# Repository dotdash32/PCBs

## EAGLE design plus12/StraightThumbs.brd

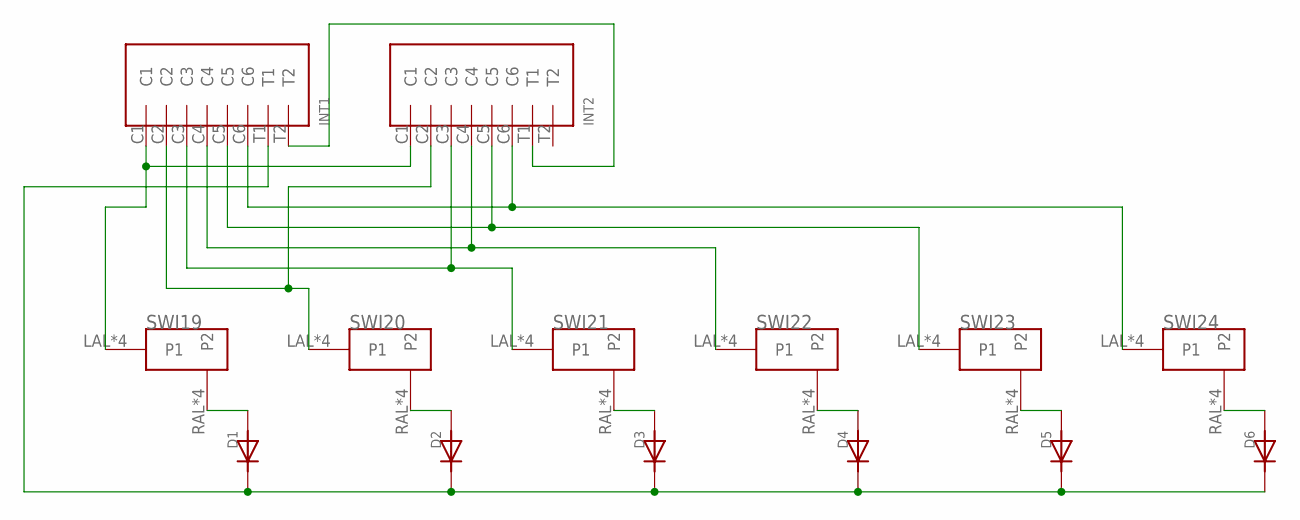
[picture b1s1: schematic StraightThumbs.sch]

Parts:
D1, D2, D3, D4, D5, D6: DIODE; DIODE_COMBO
INT1, INT2: INTRCNNT
SWI19, SWI20, SWI21, SWI22, SWI23, SWI24: MX/ALPSDOUBLESIDED; DOUBLED_MX/ALPS

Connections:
unnamed: D1.ANOSB (AN), D1.ANOST (AN), D1.ANOT (AN), SWI19.RAL (P2), SWI19.RAR (P2), SWI19.RCL (P2), SWI19.RCR (P2)
unnamed: D2.ANOSB (AN), D2.ANOST (AN), D2.ANOT (AN), SWI20.RAL (P2), SWI20.RAR (P2), SWI20.RCL (P2), SWI20.RCR (P2)
unnamed: D3.ANOSB (AN), D3.ANOST (AN), D3.ANOT (AN), SWI21.RAL (P2), SWI21.RAR (P2), SWI21.RCL (P2), SWI21.RCR (P2)
unnamed: D4.ANOSB (AN), D4.ANOST (AN), D4.ANOT (AN), SWI22.RAL (P2), SWI22.RAR (P2), SWI22.RCL (P2), SWI22.RCR (P2)
unnamed: D5.ANOSB (AN), D5.ANOST (AN), D5.ANOT (AN), SWI23.RAL (P2), SWI23.RAR (P2), SWI23.RCL (P2), SWI23.RCR (P2)
unnamed: D6.ANOSB (AN), D6.ANOST (AN), D6.ANOT (AN), SWI24.RAL (P2), SWI24.RAR (P2), SWI24.RCL (P2), SWI24.RCR (P2)
unnamed: INT1.C1, INT2.C1, SWI19.LAL (P1), SWI19.LAR (P1), SWI19.LCL (P1), SWI19.LCR (P1)
unnamed: INT1.C2, INT2.C2, SWI20.LAL (P1), SWI20.LAR (P1), SWI20.LCL (P1), SWI20.LCR (P1)
unnamed: INT1.C3, INT2.C3, SWI21.LAL (P1), SWI21.LAR (P1), SWI21.LCL (P1), SWI21.LCR (P1)
unnamed: INT1.C4, INT2.C4, SWI22.LAL (P1), SWI22.LAR (P1), SWI22.LCL (P1), SWI22.LCR (P1)
unnamed: INT1.C5, INT2.C5, SWI23.LAL (P1), SWI23.LAR (P1), SWI23.LCL (P1), SWI23.LCR (P1)
unnamed: INT1.C6, INT2.C6, SWI24.LAL (P1), SWI24.LAR (P1), SWI24.LCL (P1), SWI24.LCR (P1)
unnamed: D1.CATSB (CAT), D1.CATST (CAT), D1.CATT (CAT), D2.CATSB (CAT), D2.CATST (CAT), D2.CATT (CAT), D3.CATSB (CAT), D3.CATST (CAT), D3.CATT (CAT), D4.CATSB (CAT), D4.CATST (CAT), D4.CATT (CAT), D5.CATSB (CAT), D5.CATST (CAT), D5.CATT (CAT), D6.CATSB (CAT), D6.CATST (CAT), D6.CATT (CAT), INT1.T1
unnamed: INT1.T2, INT2.T1

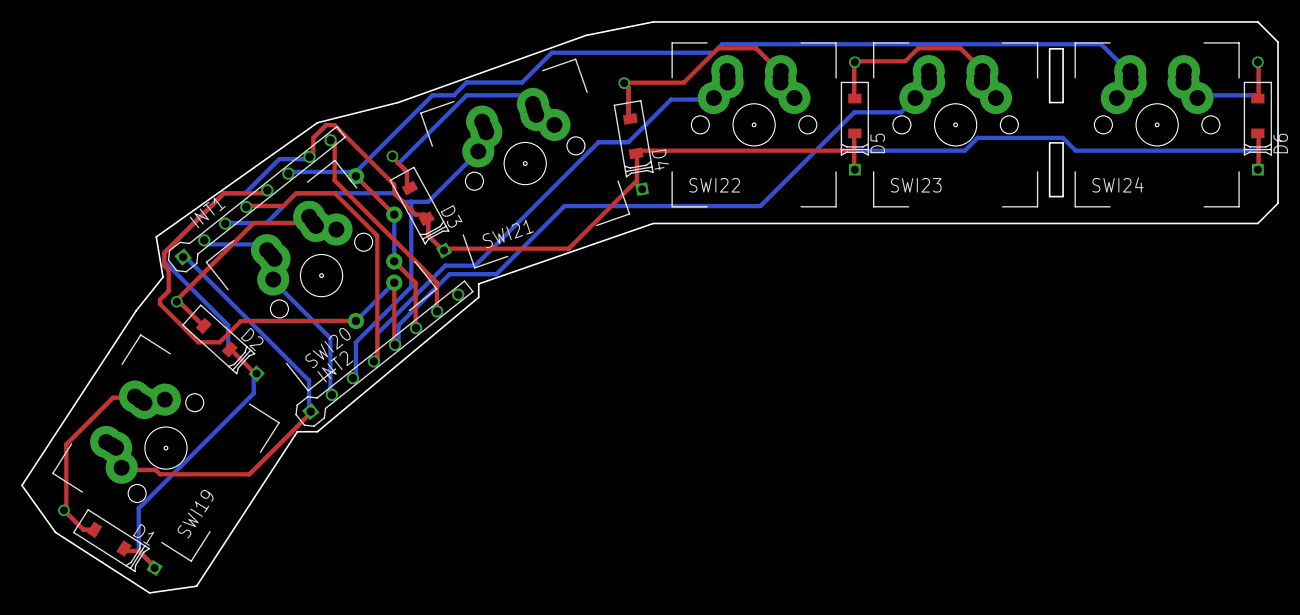
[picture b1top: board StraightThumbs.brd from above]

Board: 2 copper layers, 118.7 x 54.0 mm, 14 parts (0 on the bottom side), 14 nets.

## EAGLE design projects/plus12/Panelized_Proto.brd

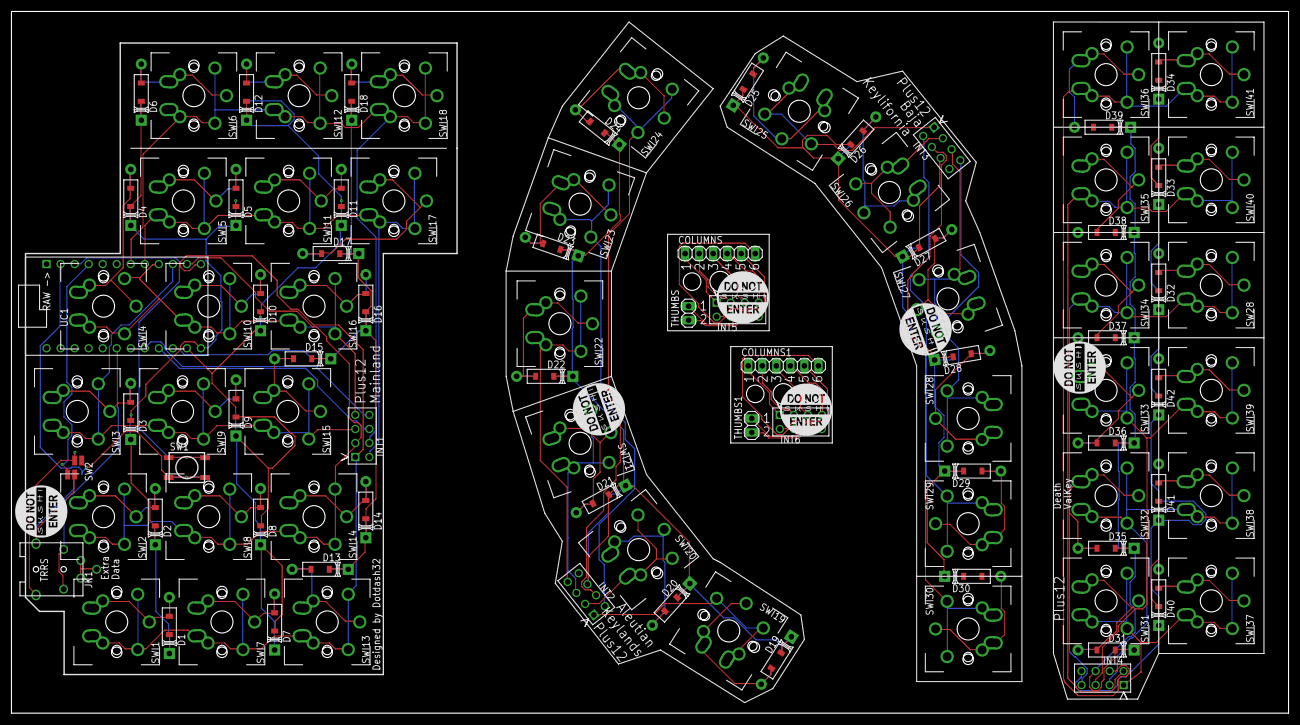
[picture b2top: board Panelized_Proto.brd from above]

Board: 2 copper layers, 231.1 x 127.0 mm, 108 parts (0 on the bottom side), 98 nets.

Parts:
COLUMNS, COLUMNS1: 1X06
D1, D2, D3, D4, D5, D6, D7, D8, D9, D10, D11, D12, D13, D14, D15, D16, D17, D18, D19, D20, D21, D22, D23, D24, D25, D26, D27, D28, D29, D30, D31, D32, D33, D34, D35, D36, D37, D38, D39, D40, D41, D42: DIODE; DIODE_COMBO
INT1, INT2, INT3, INT4, INT5, INT6: INTRCNNT4X2; INTRRIBBON
JK1: TRRSJACKUNDER; TRRSJACK
SW1: RSTSWSMD; FLATSWT
SW2: TRANSFERPADDY; TRANSFER_PADS
SW28: MX/ALPSDOUBLESIDED; DOUBLED_MX/ALPS
SWI1, SWI2, SWI3, SWI4, SWI5, SWI6, SWI7, SWI8, SWI9, SWI10, SWI11, SWI12, SWI13, SWI14, SWI15, SWI16, SWI17, SWI18, SWI19, SWI20, SWI21, SWI22, SWI23, SWI24, SWI25, SWI26, SWI27, SWI28, SWI29, SWI30, SWI31, SWI32, SWI33, SWI34, SWI35, SWI36, SWI37, SWI38, SWI39, SWI40, SWI41: MX/ALPSDOUBLESIDED; DOUBLED_MX/ALPS
THUMBS, THUMBS1: 1X02
U$1, U$4, U$6, U$7: 3_8INCH_BOT
U$2, U$3, U$5, U$8, U$9, U$10: 3_8INCH_TOP
UC1: PROMICROUNDER; PROMICRO_UNDER

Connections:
unnamed: INT1.C5, SWI5.LAL, SWI5.LAR, SWI5.LCL, SWI5.LCR, SWI5.LLP, SWI5.LRLP, SWI11.LAL, SWI11.LAR, SWI11.LCL, SWI11.LCR, SWI11.LLP, SWI11.LRLP, SWI17.LAL, SWI17.LAR, SWI17.LCL, SWI17.LCR, SWI17.LLP, SWI17.LRLP, UC1.P$17
unnamed: D1.ANOSB, D1.ANOST, D1.ANOT, SWI1.RAL, SWI1.RAR, SWI1.RCL, SWI1.RCR, SWI1.RLMID
unnamed: D2.ANOSB, D2.ANOST, D2.ANOT, SWI2.RAL, SWI2.RAR, SWI2.RCL, SWI2.RCR, SWI2.RLMID
unnamed: D3.ANOSB, D3.ANOST, D3.ANOT, SWI3.RAL, SWI3.RAR, SWI3.RCL, SWI3.RCR, SWI3.RLMID
unnamed: D4.ANOSB, D4.ANOST, D4.ANOT, SWI4.RAL, SWI4.RAR, SWI4.RCL, SWI4.RCR, SWI4.RLMID
unnamed: D5.ANOSB, D5.ANOST, D5.ANOT, SWI5.RAL, SWI5.RAR, SWI5.RCL, SWI5.RCR, SWI5.RLMID
unnamed: D6.ANOSB, D6.ANOST, D6.ANOT, SWI6.RAL, SWI6.RAR, SWI6.RCL, SWI6.RCR, SWI6.RLMID
unnamed: D7.ANOSB, D7.ANOST, D7.ANOT, SWI7.RAL, SWI7.RAR, SWI7.RCL, SWI7.RCR, SWI7.RLMID
unnamed: D8.ANOSB, D8.ANOST, D8.ANOT, SWI8.RAL, SWI8.RAR, SWI8.RCL, SWI8.RCR, SWI8.RLMID
unnamed: D9.ANOSB, D9.ANOST, D9.ANOT, SWI9.RAL, SWI9.RAR, SWI9.RCL, SWI9.RCR, SWI9.RLMID
unnamed: D10.ANOSB, D10.ANOST, D10.ANOT, SWI10.RAL, SWI10.RAR, SWI10.RCL, SWI10.RCR, SWI10.RLMID
unnamed: D11.ANOSB, D11.ANOST, D11.ANOT, SWI11.RAL, SWI11.RAR, SWI11.RCL, SWI11.RCR, SWI11.RLMID
unnamed: D12.ANOSB, D12.ANOST, D12.ANOT, SWI12.RAL, SWI12.RAR, SWI12.RCL, SWI12.RCR, SWI12.RLMID
unnamed: D13.ANOSB, D13.ANOST, D13.ANOT, SWI13.RAL, SWI13.RAR, SWI13.RCL, SWI13.RCR, SWI13.RLMID
unnamed: D14.ANOSB, D14.ANOST, D14.ANOT, SWI14.RAL, SWI14.RAR, SWI14.RCL, SWI14.RCR, SWI14.RLMID
unnamed: D15.ANOSB, D15.ANOST, D15.ANOT, SWI15.RAL, SWI15.RAR, SWI15.RCL, SWI15.RCR, SWI15.RLMID
unnamed: D16.ANOSB, D16.ANOST, D16.ANOT, SWI16.RAL, SWI16.RAR, SWI16.RCL, SWI16.RCR, SWI16.RLMID
unnamed: D17.ANOSB, D17.ANOST, D17.ANOT, SWI17.RAL, SWI17.RAR, SWI17.RCL, SWI17.RCR, SWI17.RLMID
unnamed: D18.ANOSB, D18.ANOST, D18.ANOT, SWI18.RAL, SWI18.RAR, SWI18.RCL, SWI18.RCR, SWI18.RLMID
unnamed: D1.CATSB, D1.CATST, D1.CATT, D2.CATSB, D2.CATST, D2.CATT, D3.CATSB, D3.CATST, D3.CATT, D4.CATSB, D4.CATST, D4.CATT, D5.CATSB, D5.CATST, D5.CATT, D6.CATSB, D6.CATST, D6.CATT, UC1.P$12
unnamed: D7.CATSB, D7.CATST, D7.CATT, D8.CATSB, D8.CATST, D8.CATT, D9.CATSB, D9.CATST, D9.CATT, D10.CATSB, D10.CATST, D10.CATT, D11.CATSB, D11.CATST, D11.CATT, D12.CATSB, D12.CATST, D12.CATT, UC1.P$11
unnamed: D13.CATSB, D13.CATST, D13.CATT, D14.CATSB, D14.CATST, D14.CATT, D15.CATSB, D15.CATST, D15.CATT, D16.CATSB, D16.CATST, D16.CATT, D17.CATSB, D17.CATST, D17.CATT, D18.CATSB, D18.CATST, D18.CATT, UC1.P$10
unnamed: INT1.C1, SWI1.LAL, SWI1.LAR, SWI1.LCL, SWI1.LCR, SWI1.LLP, SWI1.LRLP, SWI7.LAL, SWI7.LAR, SWI7.LCL, SWI7.LCR, SWI7.LLP, SWI7.LRLP, SWI13.LAL, SWI13.LAR, SWI13.LCL, SWI13.LCR, SWI13.LLP, SWI13.LRLP, UC1.P$13
unnamed: INT1.C2, SWI2.LAL, SWI2.LAR, SWI2.LCL, SWI2.LCR, SWI2.LLP, SWI2.LRLP, SWI8.LAL, SWI8.LAR, SWI8.LCL, SWI8.LCR, SWI8.LLP, SWI8.LRLP, SWI14.LAL, SWI14.LAR, SWI14.LCL, SWI14.LCR, SWI14.LLP, SWI14.LRLP, UC1.P$14
unnamed: INT1.C3, SWI3.LAL, SWI3.LAR, SWI3.LCL, SWI3.LCR, SWI3.LLP, SWI3.LRLP, SWI9.LAL, SWI9.LAR, SWI9.LCL, SWI9.LCR, SWI9.LLP, SWI9.LRLP, SWI15.LAL, SWI15.LAR, SWI15.LCL, SWI15.LCR, SWI15.LLP, SWI15.LRLP, UC1.P$15
unnamed: INT1.C4, SWI4.LAL, SWI4.LAR, SWI4.LCL, SWI4.LCR, SWI4.LLP, SWI4.LRLP, SWI10.LAL, SWI10.LAR, SWI10.LCL, SWI10.LCR, SWI10.LLP, SWI10.LRLP, SWI16.LAL, SWI16.LAR, SWI16.LCL, SWI16.LCR, SWI16.LLP, SWI16.LRLP, UC1.P$16
unnamed: INT1.C6, SWI6.LAL, SWI6.LAR, SWI6.LCL, SWI6.LCR, SWI6.LLP, SWI6.LRLP, SWI12.LAL, SWI12.LAR, SWI12.LCL, SWI12.LCR, SWI12.LLP, SWI12.LRLP, SWI18.LAL, SWI18.LAR, SWI18.LCL, SWI18.LCR, SWI18.LLP, SWI18.LRLP, UC1.P$18
unnamed: SW2.VCCB, SW2.VCCT, UC1.P$21
unnamed: INT1.T1, UC1.P$9
unnamed: JK1.4B, JK1.4T, SW2.IN4B, SW2.IN4T
unnamed: JK1.1B, JK1.1T, SW2.IN1B, SW2.IN1T
unnamed: JK1.2B, JK1.2T, UC1.P$6
unnamed: INT1.T2, UC1.P$8
unnamed: SW1.P$3, SW1.P$4, SW1.P$7, SW1.P$8, UC1.P$22
unnamed: SW1.P$1, SW1.P$2, SW1.P$5, SW1.P$6, SW2.GNDB, SW2.GNDT, UC1.P$23
unnamed: JK1.3B, JK1.3T, JK1.EXTRA_DATA
unnamed: D19.ANOSB, D19.ANOST, D19.ANOT, SWI19.RAL, SWI19.RAR, SWI19.RCL, SWI19.RCR, SWI19.RLMID
unnamed: D20.ANOSB, D20.ANOST, D20.ANOT, SWI20.RAL, SWI20.RAR, SWI20.RCL, SWI20.RCR, SWI20.RLMID
unnamed: D21.ANOSB, D21.ANOST, D21.ANOT, SWI21.RAL, SWI21.RAR, SWI21.RCL, SWI21.RCR, SWI21.RLMID
unnamed: D22.ANOSB, D22.ANOST, D22.ANOT, SWI22.RAL, SWI22.RAR, SWI22.RCL, SWI22.RCR, SWI22.RLMID
unnamed: D23.ANOSB, D23.ANOST, D23.ANOT, SWI23.RAL, SWI23.RAR, SWI23.RCL, SWI23.RCR, SWI23.RLMID
unnamed: D24.ANOSB, D24.ANOST, D24.ANOT, SWI24.RAL, SWI24.RAR, SWI24.RCL, SWI24.RCR, SWI24.RLMID
unnamed: INT2.C1, SWI19.LAL, SWI19.LAR, SWI19.LCL, SWI19.LCR, SWI19.LLP, SWI19.LRLP
unnamed: INT2.C2, SWI20.LAL, SWI20.LAR, SWI20.LCL, SWI20.LCR, SWI20.LLP, SWI20.LRLP
unnamed: INT2.C3, SWI21.LAL, SWI21.LAR, SWI21.LCL, SWI21.LCR, SWI21.LLP, SWI21.LRLP
unnamed: INT2.C4, SWI22.LAL, SWI22.LAR, SWI22.LCL, SWI22.LCR, SWI22.LLP, SWI22.LRLP
unnamed: INT2.C5, SWI23.LAL, SWI23.LAR, SWI23.LCL, SWI23.LCR, SWI23.LLP, SWI23.LRLP
unnamed: INT2.C6, SWI24.LAL, SWI24.LAR, SWI24.LCL, SWI24.LCR, SWI24.LLP, SWI24.LRLP
unnamed: D19.CATSB, D19.CATST, D19.CATT, D20.CATSB, D20.CATST, D20.CATT, D21.CATSB, D21.CATST, D21.CATT, D22.CATSB, D22.CATST, D22.CATT, D23.CATSB, D23.CATST, D23.CATT, D24.CATSB, D24.CATST, D24.CATT, INT2.T1
unnamed: D25.ANOSB, D25.ANOST, D25.ANOT, SWI25.RAL, SWI25.RAR, SWI25.RCL, SWI25.RCR, SWI25.RLMID
unnamed: D26.ANOSB, D26.ANOST, D26.ANOT, SWI26.RAL, SWI26.RAR, SWI26.RCL, SWI26.RCR, SWI26.RLMID
unnamed: D27.ANOSB, D27.ANOST, D27.ANOT, SWI27.RAL, SWI27.RAR, SWI27.RCL, SWI27.RCR, SWI27.RLMID
unnamed: D28.ANOSB, D28.ANOST, D28.ANOT, SWI28.RAL, SWI28.RAR, SWI28.RCL, SWI28.RCR, SWI28.RLMID
unnamed: D29.ANOSB, D29.ANOST, D29.ANOT, SWI29.RAL, SWI29.RAR, SWI29.RCL, SWI29.RCR, SWI29.RLMID
unnamed: D30.ANOSB, D30.ANOST, D30.ANOT, SWI30.RAL, SWI30.RAR, SWI30.RCL, SWI30.RCR, SWI30.RLMID
unnamed: INT3.C1, SWI25.LAL, SWI25.LAR, SWI25.LCL, SWI25.LCR, SWI25.LLP, SWI25.LRLP
unnamed: INT3.C2, SWI26.LAL, SWI26.LAR, SWI26.LCL, SWI26.LCR, SWI26.LLP, SWI26.LRLP
unnamed: INT3.C3, SWI27.LAL, SWI27.LAR, SWI27.LCL, SWI27.LCR, SWI27.LLP, SWI27.LRLP
unnamed: INT3.C4, SWI28.LAL, SWI28.LAR, SWI28.LCL, SWI28.LCR, SWI28.LLP, SWI28.LRLP
unnamed: INT3.C5, SWI29.LAL, SWI29.LAR, SWI29.LCL, SWI29.LCR, SWI29.LLP, SWI29.LRLP
unnamed: INT3.C6, SWI30.LAL, SWI30.LAR, SWI30.LCL, SWI30.LCR, SWI30.LLP, SWI30.LRLP
unnamed: D25.CATSB, D25.CATST, D25.CATT, D26.CATSB, D26.CATST, D26.CATT, D27.CATSB, D27.CATST, D27.CATT, D28.CATSB, D28.CATST, D28.CATT, D29.CATSB, D29.CATST, D29.CATT, D30.CATSB, D30.CATST, D30.CATT, INT3.T1
unnamed: D31.ANOSB, D31.ANOST, D31.ANOT, SWI31.RAL, SWI31.RAR, SWI31.RCL, SWI31.RCR, SWI31.RLMID
unnamed: D35.ANOSB, D35.ANOST, D35.ANOT, SWI32.RAL, SWI32.RAR, SWI32.RCL, SWI32.RCR, SWI32.RLMID
unnamed: D36.ANOSB, D36.ANOST, D36.ANOT, SWI33.RAL, SWI33.RAR, SWI33.RCL, SWI33.RCR, SWI33.RLMID
unnamed: D37.ANOSB, D37.ANOST, D37.ANOT, SWI34.RAL, SWI34.RAR, SWI34.RCL, SWI34.RCR, SWI34.RLMID
unnamed: D38.ANOSB, D38.ANOST, D38.ANOT, SWI35.RAL, SWI35.RAR, SWI35.RCL, SWI35.RCR, SWI35.RLMID
unnamed: D39.ANOSB, D39.ANOST, D39.ANOT, SWI36.RAL, SWI36.RAR, SWI36.RCL, SWI36.RCR, SWI36.RLMID
unnamed: D40.ANOSB, D40.ANOST, D40.ANOT, SWI37.RAL, SWI37.RAR, SWI37.RCL, SWI37.RCR, SWI37.RLMID
unnamed: D41.ANOSB, D41.ANOST, D41.ANOT, SWI38.RAL, SWI38.RAR, SWI38.RCL, SWI38.RCR, SWI38.RLMID
unnamed: D42.ANOSB, D42.ANOST, D42.ANOT, SWI39.RAL, SWI39.RAR, SWI39.RCL, SWI39.RCR, SWI39.RLMID
unnamed: D32.ANOSB, D32.ANOST, D32.ANOT, SW28.RAL, SW28.RAR, SW28.RCL, SW28.RCR, SW28.RLMID
unnamed: D33.ANOSB, D33.ANOST, D33.ANOT, SWI40.RAL, SWI40.RAR, SWI40.RCL, SWI40.RCR, SWI40.RLMID
unnamed: D34.ANOSB, D34.ANOST, D34.ANOT, SWI41.RAL, SWI41.RAR, SWI41.RCL, SWI41.RCR, SWI41.RLMID
unnamed: D32.CATSB, D32.CATST, D32.CATT, D33.CATSB, D33.CATST, D33.CATT, D34.CATSB, D34.CATST, D34.CATT, D40.CATSB, D40.CATST, D40.CATT, D41.CATSB, D41.CATST, D41.CATT, D42.CATSB, D42.CATST, D42.CATT, INT4.T2
unnamed: INT4.C1, SWI31.LAL, SWI31.LAR, SWI31.LCL, SWI31.LCR, SWI31.LLP, SWI31.LRLP, SWI37.LAL, SWI37.LAR, SWI37.LCL, SWI37.LCR, SWI37.LLP, SWI37.LRLP
unnamed: INT4.C2, SWI32.LAL, SWI32.LAR, SWI32.LCL, SWI32.LCR, SWI32.LLP, SWI32.LRLP, SWI38.LAL, SWI38.LAR, SWI38.LCL, SWI38.LCR, SWI38.LLP, SWI38.LRLP
unnamed: INT4.C3, SWI33.LAL, SWI33.LAR, SWI33.LCL, SWI33.LCR, SWI33.LLP, SWI33.LRLP, SWI39.LAL, SWI39.LAR, SWI39.LCL, SWI39.LCR, SWI39.LLP, SWI39.LRLP
unnamed: INT4.C4, SW28.LAL, SW28.LAR, SW28.LCL, SW28.LCR, SW28.LLP, SW28.LRLP, SWI34.LAL, SWI34.LAR, SWI34.LCL, SWI34.LCR, SWI34.LLP, SWI34.LRLP
unnamed: INT4.C5, SWI35.LAL, SWI35.LAR, SWI35.LCL, SWI35.LCR, SWI35.LLP, SWI35.LRLP, SWI40.LAL, SWI40.LAR, SWI40.LCL, SWI40.LCR, SWI40.LLP, SWI40.LRLP
unnamed: INT4.C6, SWI36.LAL, SWI36.LAR, SWI36.LCL, SWI36.LCR, SWI36.LLP, SWI36.LRLP, SWI41.LAL, SWI41.LAR, SWI41.LCL, SWI41.LCR, SWI41.LLP, SWI41.LRLP
unnamed: D31.CATSB, D31.CATST, D31.CATT, D35.CATSB, D35.CATST, D35.CATT, D36.CATSB, D36.CATST, D36.CATT, D37.CATSB, D37.CATST, D37.CATT, D38.CATSB, D38.CATST, D38.CATT, D39.CATSB, D39.CATST, D39.CATT, INT4.T1
unnamed: COLUMNS.1, INT5.C1
unnamed: COLUMNS.2, INT5.C2
unnamed: COLUMNS.3, INT5.C3
unnamed: COLUMNS.4, INT5.C4
unnamed: COLUMNS.5, INT5.C5
unnamed: COLUMNS.6, INT5.C6
unnamed: INT5.T1, THUMBS.1
unnamed: INT5.T2, THUMBS.2
unnamed: COLUMNS1.1, INT6.C1
unnamed: COLUMNS1.2, INT6.C2
unnamed: COLUMNS1.3, INT6.C3
unnamed: COLUMNS1.4, INT6.C4
unnamed: COLUMNS1.5, INT6.C5
unnamed: COLUMNS1.6, INT6.C6
unnamed: INT6.T1, THUMBS1.1
unnamed: INT6.T2, THUMBS1.2
